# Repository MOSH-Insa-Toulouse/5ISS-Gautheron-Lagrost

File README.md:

# Creating a shield to send data from a SGS24ISS gas sensor to a LoRaWAN Network

Authors: Arthur Gautheron, Olivier Lagrost

## 📝 Objectives and Block Diagram

The final objective of the Smart Devices UF is to "design and build a smart device based on the combination of a gas sensor and an electronic card to communicate information over a low speed network". It is a pluridisciplinary subject that combines skills from all educational backgrounds included in the PTP. GP (physics) students are best at designing a PCB and creating datasheets. AE (electronics) students, such as ourselves, prefer electrical schematics, embedded programming and have a better understanding of how to design the whole system overall. Finally, IR (computer science) students are better at understanding how to communicate data over LoRaWAN.

This repository aims at explaining our work on this system.

SGS24ISS is the name we decided to give to our homemade gas sensor. It stands for "Smart Gas Sensor 2024 Innovative Smart Systems". The objective of the project is to collect data from the smart sensor, monitor its internal temperature for optimal measurements, and send the collected data over LoRa to a Chirpstack server to be processed and used in an eventual application.

## 🧑‍🔬 Sensor design and creation

The SGS24ISS gas sensor is capable of detecting the presence of several gases depending on their concentration. The sensor is able to perform multiple tasks:
* Returns current that depends on the concentration of gas around the sensor.
* Measure its own internal temperature.
* Increase its own temperature with an integrated heater.

For more information about the sensor, please read its datasheet [here](https://github.com/Timanoin/lora_app/blob/main/datasheet.pdf).

## 💻 Sensor Acquisition System

To collect data from the sensor, the current emitted by the sensor must be transformed into voltage, since MCUs cannot acquire current intensity. The system developed to acquire this information is a transimpedance amplifier.
The  contains the schematic of such an acquisition system, as well as other simulations to model the gas sensor.

The transimpedance amplifier is composed of 4 stages.
* Low-pass filter of cut-off frequency 16Hz to remove noise from the sensor.
* Low-pass filter of cut-off frequency 1.6Hz to remove noise from the mains supply.
* Non-inverting amplifier.
* Low-pass filter of cut-off frequency 1600Hz as an anti-aliasing filter.

The resistance of the gas sensor is determined as follows:

## ✏️ Shield Electrical Schematic

The schematics tested in simulation with LTSpice are recreated into KiCad for future PCB creation. All pins from the SGS24ISS (gas sensor, temperature sensor, heater) are connected to the Arduino pins. The RN2483 LoRa communication chip and its antenna are also connected to the Arduino in the schematic.
The KiCad files can be found .

## ⚡ Shield PCB Design

The PCB is routed on the bottom layer, since pins of THT components must be soldered on the copper covered side of the PCB.

The resulting PCB is pretty small, but it could be even smaller if another MCU was used for data acquisition (like an Arduino Nano or a STM32).

## 💻 Arduino Uno Embedded Software

We first set up our LoRa communication and we initialize the pins for the sensor and the Uart to communicate with our chip. Thus we have two serial communications, “Serial” between the computer and the Arduino and “mySerial” between the Arduino and the RN2483A. We also define the threshold on the sensor value above which we start transmitting our data, meaning that the gas quantity is dangerous. 

In order to communicate by LoRa we have to set it up. We wait for our RN2483A to start and check if we can communicate by LoRa. To this end, we print the Hardware EUI (HWEUI) which is the ID of our RN2483 and that we need to register our device on Chirpstack. 

We now have to establish communication with Chirpstack using the Over The Air Authentication (OTAA) method to connect to the network. To this end, we need the appEui and the appKey found on the Chirpstack website when registering our device. and the function ”initOTAA(appEui, appKey)” to connect. 

## 📻 ChirpStack

On the Chirp Stack side, we create a profile and add a device to get the JoinEui ( = appEui) and the appKey. 
Once we are connected we can start sending the data from our sensor. 
As specified at the beginning, we only send data when an overshoot to the threshold happens. 

We can see that we are connected to Chirpstack, our device is enabled and sending data in ASCII

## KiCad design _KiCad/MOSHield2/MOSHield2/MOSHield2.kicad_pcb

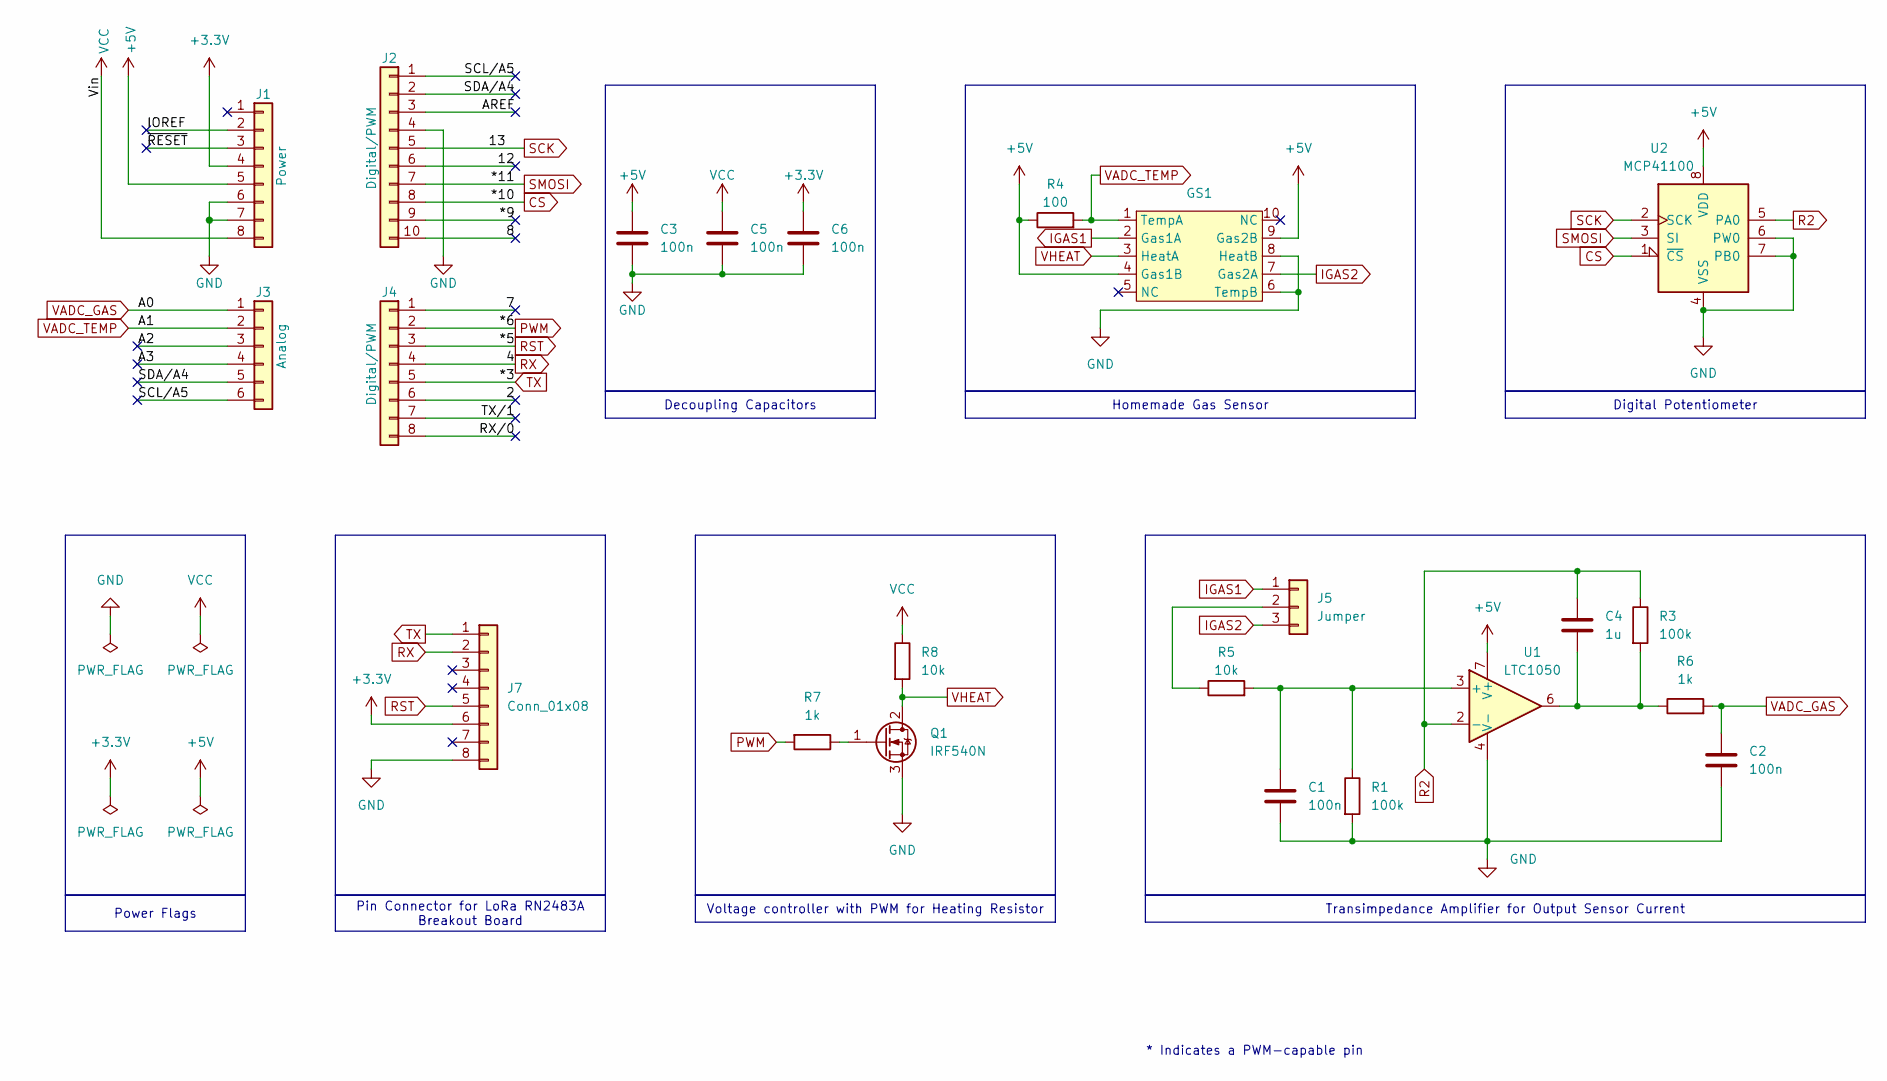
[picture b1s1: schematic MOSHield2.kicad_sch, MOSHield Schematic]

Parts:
C1, C2, C3, C5, C6: 100n; C_Disc_D4.7mm_W2.5mm_P5.00mm
C4: 1u; C_Rect_L7.0mm_W4.5mm_P5.00mm
GS1: TO-5-10
J1: Power; PinSocket_1x08_P2.54mm_Vertical
J2: Digital/PWM; PinSocket_1x10_P2.54mm_Vertical
J3: Analog; PinSocket_1x06_P2.54mm_Vertical
J4: Digital/PWM; PinSocket_1x08_P2.54mm_Vertical
J5: Jumper; PinHeader_1x03_P2.54mm_Vertical
J7: Conn_01x08; PinSocket_1x08_P2.54mm_Vertical
Q1: IRF540N; TO-220-3_Vertical
R1, R3: 100k; R_Axial_DIN0207_L6.3mm_D2.5mm_P10.16mm_Horizontal
R4: 100; R_Axial_DIN0207_L6.3mm_D2.5mm_P10.16mm_Horizontal
R5, R8: 10k; R_Axial_DIN0207_L6.3mm_D2.5mm_P10.16mm_Horizontal
R6, R7: 1k; R_Axial_DIN0207_L6.3mm_D2.5mm_P10.16mm_Horizontal
U1: LTC1050; DIP-8_W7.62mm
U2: MCP41100; DIP-8_W7.62mm

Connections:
+3.3V: C6.1, J1.4, J7.6
+5V: C3.1, GS1.4 (Gas1B), GS1.9 (Gas2B), J1.5, R4.1, U1.7 (V+), U2.8 (VDD)
/2: J4.6
/7: J4.1
/8: J2.10
/12: J2.6
/*9: J2.9
/A2: J3.3
/A3: J3.4
/AREF: J2.3
/IOREF: J1.2
/RX/0: J4.8
/SCL/A5: J2.1, J3.6
/SDA/A4: J2.2, J3.5
/TX/1: J4.7
/~RESET: J1.3
CS: J2.8, U2.1 (~CS)
GND: C1.2, C2.2, C3.2, C5.2, C6.2, GS1.6 (TempB), GS1.8 (HeatB), J1.6, J1.7, J2.4, J7.8, Q1.3 (S), R1.2, U1.4 (V-), U2.4 (VSS), U2.6 (PW0), U2.7 (PB0)
IGAS1: GS1.2 (Gas1A), J5.1
IGAS2: GS1.7 (Gas2A), J5.3
unnamed: C4.2, R3.2, R6.1, U1.6
unnamed: J5.2, R5.1
unnamed: Q1.1 (G), R7.1
unnamed: C1.1, R1.1, R5.2, U1.3 (+)
PWM: J4.2, R7.2
R2: C4.1, R3.1, U1.2 (-), U2.5 (PA0)
RST: J4.3, J7.5
RX: J4.4, J7.2
SCK: J2.5, U2.2 (SCK)
SMOSI: J2.7, U2.3 (SI)
TX: J4.5, J7.1
VADC_GAS: C2.1, J3.1, R6.2
VADC_TEMP: GS1.1 (TempA), J3.2, R4.2
VCC: C5.1, J1.8, R8.1
VHEAT: GS1.3 (HeatA), Q1.2 (D), R8.2

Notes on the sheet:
Decoupling Capacitors
Homemade Gas Sensor
Transimpedance Amplifier for Output Sensor Current
Power Flags
Voltage controller with PWM for Heating Resistor
Pin Connector for LoRa RN2483A Breakout Board
Digital Potentiometer
* Indicates a PWM-capable pin

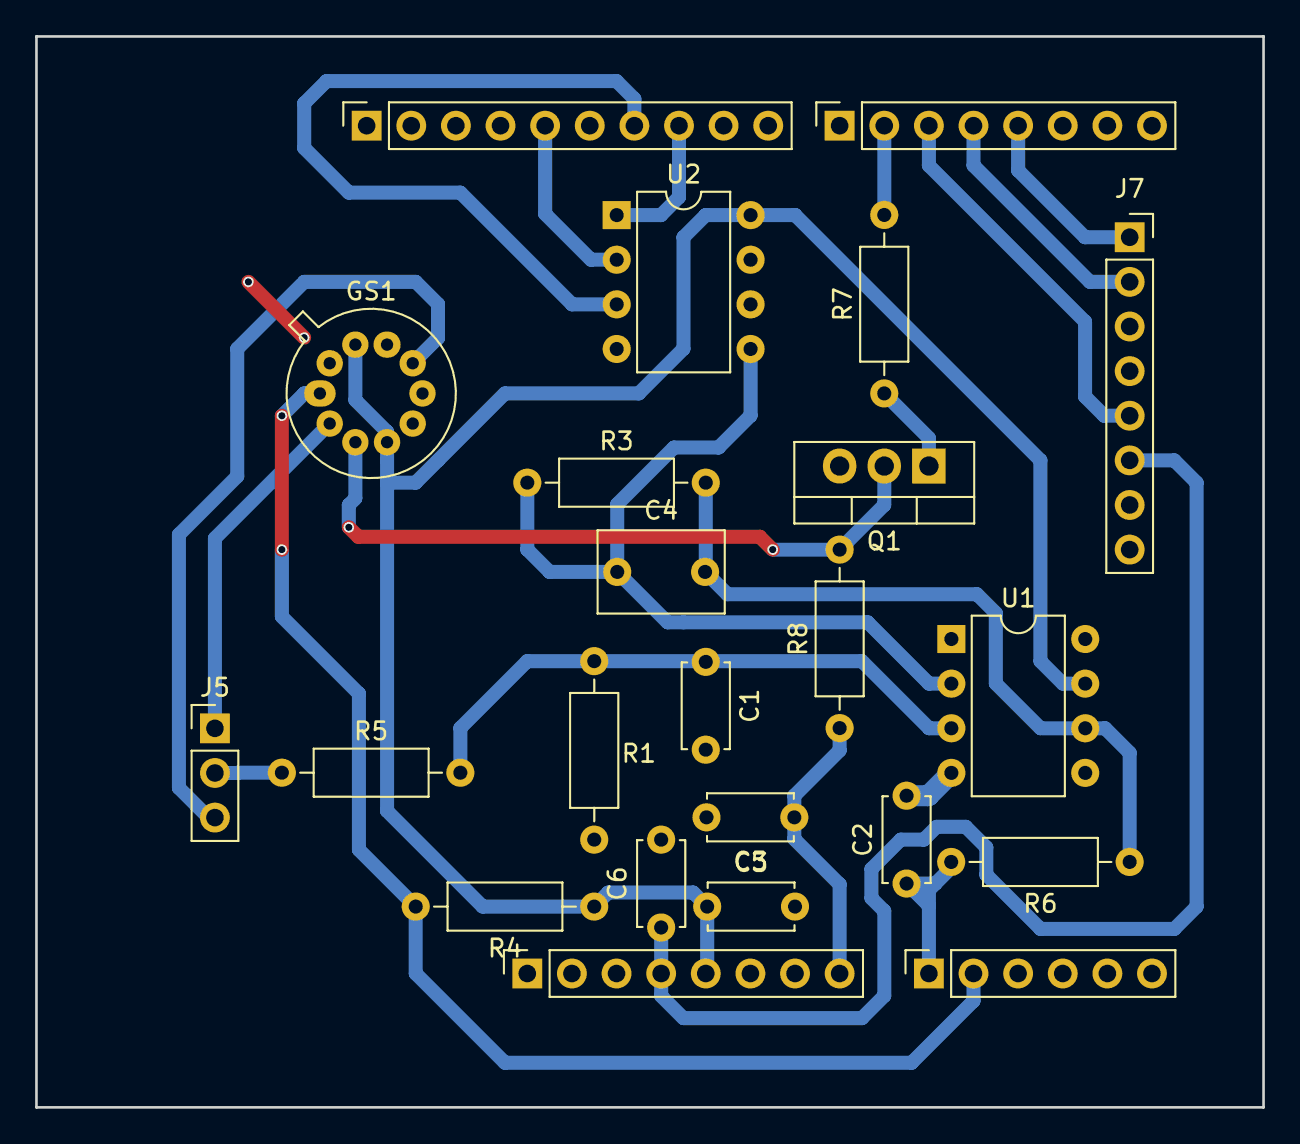
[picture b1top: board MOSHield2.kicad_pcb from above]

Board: 2 copper layers, 69.8 x 61.0 mm, 23 parts (0 on the bottom side), 23 nets.

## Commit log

2023-12-06 Added Arduino and KiCad projects
2024-02-11 Added datasheet
2024-02-11 Added block diagram image
2024-02-11 Fixed image (test)
2024-02-11 test
2024-02-11 Almost final commit
